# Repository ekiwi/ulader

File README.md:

# uLader #

This project aims at creating a backup battery powered bike
lighting system.
It borrows from the great work done by the developers of the
Forumslader and acknowledges this by incorporation
Lader (german for charger) into its name.
The u stands for the micro controller used in this design,
the use of which is going to add a lot more flexibility.

## Component Overview ##

The uLader system consists of these components:
* Main Board: atmega88 uC, ac to dc circuit, charging circuit, 
control switches
* Tail Light: red low power led (dimmable), photo transistor
* Front Light: attiny uC, white low power DLR (dimmabel), white 3W led 
(dimmable), photo transistor
* 2x Rotation Sensor: front and back

## Optional/Future Features ##
* White LED(s) underneath the saddle that can be turned on to find your locks
keyhole
* Pressure Sensor underneath/in the saddle to detect if someone is riding the
bike
* Turn signals on front and back

### Main Board ###

The main board contains the circuit that converts the power from the bike
dynamo, which acts approximately like an AC current source, to about 12V DC.
This circuit is heavily based on the awesome work done by the people behind
the [Forumslader project](forumslader.de).
This circuit is also responsible for charging the LiFePo4 accumulators used.
Check out [forumnslader.de]
(http://www.forumslader.de/Akkus-fuer-12V-Lader.189.0.html) if you want to use
different batteries.

The micro controller part of the Main Board features an atmega88. It was choosen,
because of its ease of use, its low power consumption and because if the number
of pins available.
The atmega is used for the following:
* power mangagement
    * check charging status
    * (indicate status??)
    * cut of power to all devices when battery cells run low
* lighting control
    * measure light intensity
    * measure speed
    * control which lights need to be on and how bright they need to be
    * in auto mode decide when to turn on which lights and auto dim

### Tail Light ####

The Tail Light needs to ensure visibility during the night (and day) from the 
back as well as from the side. In addition to that it must not blind other 
people.  
The CAT4201 led step down driver is used in combination with an OSRAM Top LED
in order to provide a low power solution for these requirements. The tail
light also includes a photo transistor for measuring the ambient light.  
It should be tested if visibility from the side of your bike can be enhanced
by adding one LED on each side.

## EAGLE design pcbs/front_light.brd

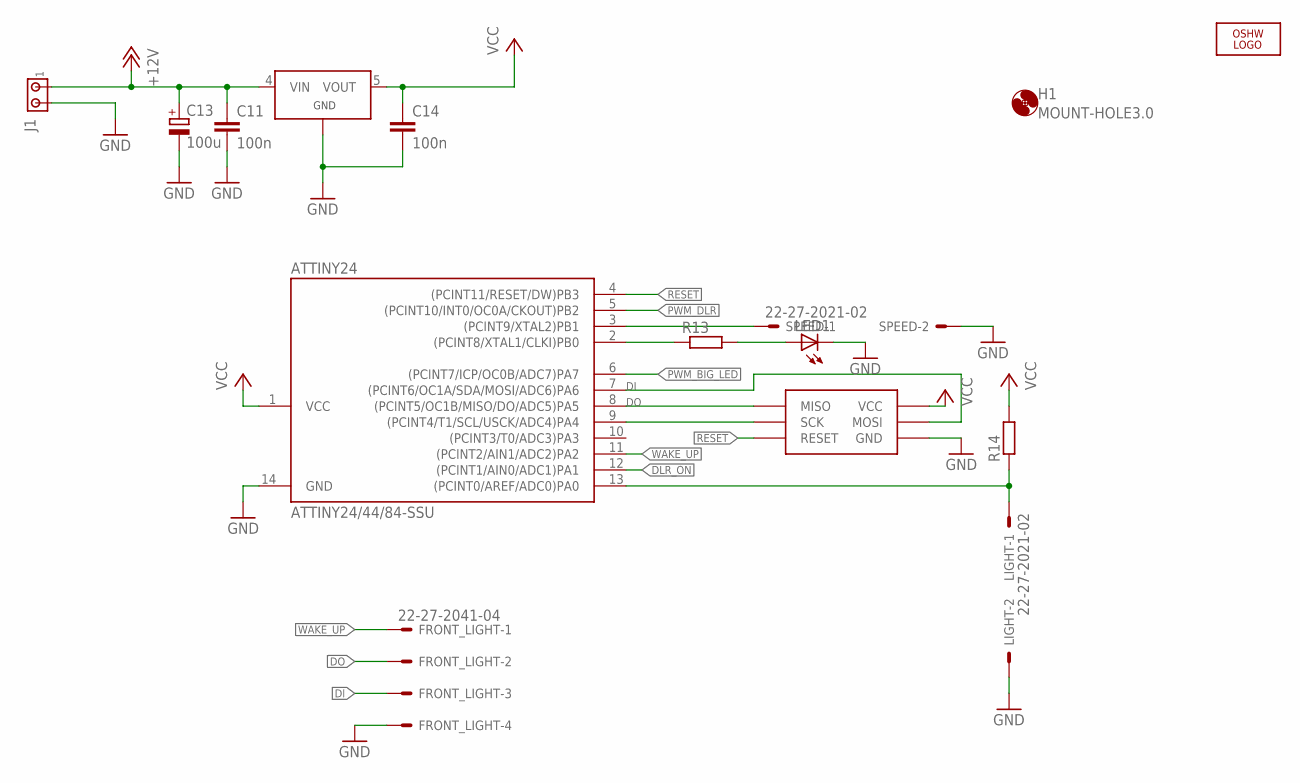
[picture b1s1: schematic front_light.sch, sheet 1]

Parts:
ATTINY24: ATTINY24/44/84-SSU; SOIC14
C11, C14: 100n; C0603
C13: 100u; PANASONIC_E
FRONT_LIGHT: 22-27-2041-04; 6410-04
H1: MOUNT-HOLE3.0; 3,0
J1: MTA02-156; 1X2MTA
LED1: LEDCHIPLED_0603; CHIPLED_0603
LIGHT: 22-27-2021-02; 6410-02
LOGO2: OSHW_LOGO_6MILX0150-NT; OSHW_6X150_NOTEXT
R13, R14: R-EU_R0603; R0603
SPEED: 22-27-2021-02; 6410-02
U$1: TPS71530; SOT23-DBV
U$2: ISP_SPECIALS; ISP_RM2_00_STRAIGHT

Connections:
+12V: C11.1, C13.+, J1.1, U$1.4 (VIN); also elsewhere on the board
DI: ATTINY24.7 ((PCINT6/OC1A/SDA/MOSI/ADC6)PA6), FRONT_LIGHT.3, U$2.MOSI
DLR_ON: ATTINY24.12 ((PCINT1/AIN0/ADC1)PA1); also elsewhere on the board
DO: ATTINY24.8 ((PCINT5/OC1B/MISO/DO/ADC5)PA5), FRONT_LIGHT.2, U$2.RESET (MISO)
GND: ATTINY24.14 (GND), C11.2, C13.-, C14.2, FRONT_LIGHT.4, J1.2, LED1.C, LIGHT.2, SPEED.2, U$1.2 (GND), U$2.VCC (GND); also elsewhere on the board
unnamed: ATTINY24.3 ((PCINT9/XTAL2)PB1), SPEED.1
unnamed: ATTINY24.9 ((PCINT4/T1/SCL/USCK/ADC4)PA4), U$2.SCK
unnamed: ATTINY24.13 ((PCINT0/AREF/ADC0)PA0), LIGHT.1, R14.1
unnamed: ATTINY24.2 ((PCINT8/XTAL1/CLKI)PB0), R13.1
unnamed: LED1.A, R13.2
PWM_BIG_LED: ATTINY24.6 ((PCINT7/ICP/OC0B/ADC7)PA7); also elsewhere on the board
PWM_DLR: ATTINY24.5 ((PCINT10/INT0/OC0A/CKOUT)PB2); also elsewhere on the board
RESET: ATTINY24.4 ((PCINT11/RESET/DW)PB3), U$2.MISO (RESET)
VCC: ATTINY24.1 (VCC), C14.1, R14.2, U$1.5 (VOUT), U$2.GND (VCC)
WAKE_UP: ATTINY24.11 ((PCINT2/AIN1/ADC2)PA2), FRONT_LIGHT.1

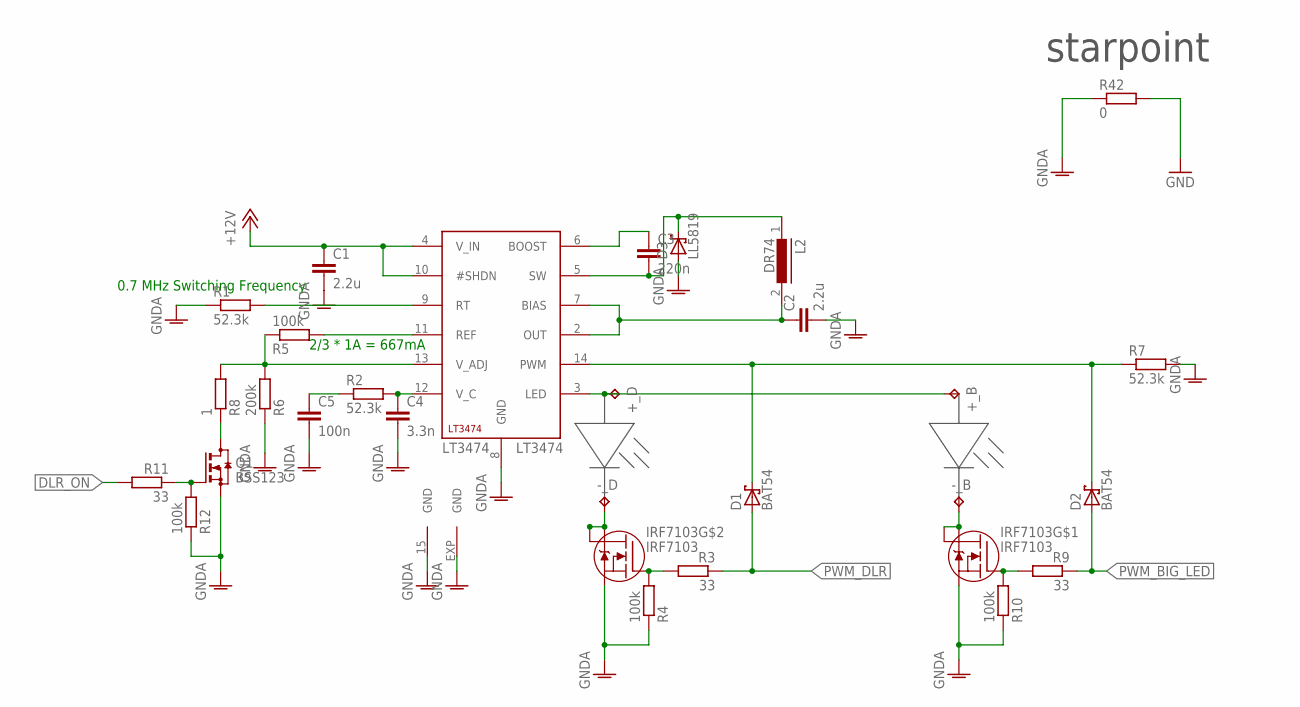
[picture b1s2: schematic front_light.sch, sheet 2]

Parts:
+_B: TPTP20SQ; TP20SQ
+_D: TPTP20SQ; TP20SQ
-_B: TPTP20SQ; TP20SQ
-_D: TPTP20SQ; TP20SQ
C1, C2: 2.2u; C0805
C3: 220n; C0603
C4: 3.3n; C0603
C5: 100n; C0603
D1, D2: BAT54; SOT23
D3: LL5819; MELF-MLL41
IRF7103: IRF7103; SO8-2
L2: DR74
LT3474: LT3474; TSSOP16_BA
Q1: BSS123; SOT23
R1, R2, R7: 52.3k; R0603
R3, R9, R11: 33; R0603
R4, R5, R10, R12: 100k; R0603
R6: 200k; R0603
R8: 1; R0603
R42: 0; R0603

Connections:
+12V: C1.1, LT3474.4 (V_IN), LT3474.10 (#SHDN); also elsewhere on the board
DLR_ON: R11.2; also elsewhere on the board
GND: R42.2; also elsewhere on the board
GNDA: C1.2, C2.2, C4.2, C5.2, D3.A, IRF7103.1 (S), IRF7103.3 (S), LT3474.8 (GND), LT3474.15 (GND), LT3474.EXP (GND), Q1.2 (S), R1.1, R4.1, R6.1, R7.2, R10.1, R12.1, R42.1
unnamed: C3.2, D3.C, L2.1, LT3474.5 (SW)
unnamed: C2.1, L2.2, LT3474.2 (OUT), LT3474.7 (BIAS)
unnamed: LT3474.11 (REF), R5.2
unnamed: LT3474.9 (RT), R1.2
unnamed: C3.1, LT3474.6 (BOOST)
unnamed: C4.1, LT3474.12 (V_C), R2.2
unnamed: C5.1, R2.1
unnamed: +_B.TP, +_D.TP, LT3474.3 (LED)
unnamed: -_D.TP, IRF7103.5 (D), IRF7103.6 (D)
unnamed: IRF7103.4 (G), R3.2, R4.2
unnamed: LT3474.13 (V_ADJ), R5.1, R6.2, R8.2
unnamed: Q1.3 (D), R8.1
unnamed: Q1.1 (G), R11.1, R12.2
unnamed: -_B.TP, IRF7103.7 (D), IRF7103.8 (D)
unnamed: IRF7103.2 (G), R9.2, R10.2
PWM: D1.3 (C), D2.3 (C), LT3474.14 (PWM), R7.1
PWM_BIG_LED: D2.1 (A), R9.1; also elsewhere on the board
PWM_DLR: D1.1 (A), R3.1; also elsewhere on the board

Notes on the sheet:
0.7 MHz Switching Frequency
2/3 * 1A = 667mA
starpoint

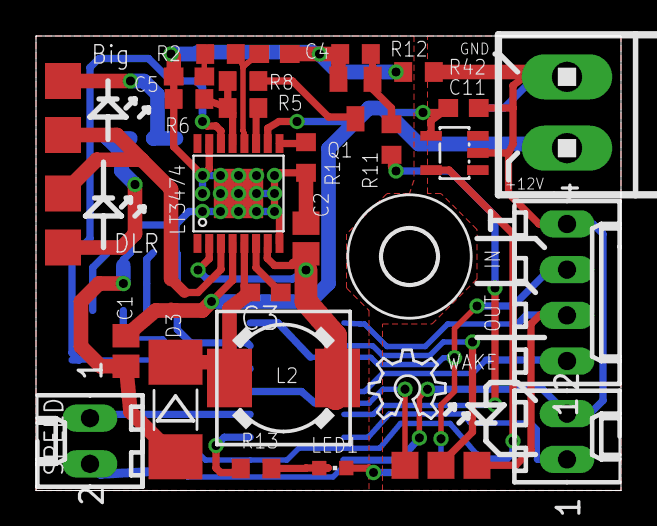
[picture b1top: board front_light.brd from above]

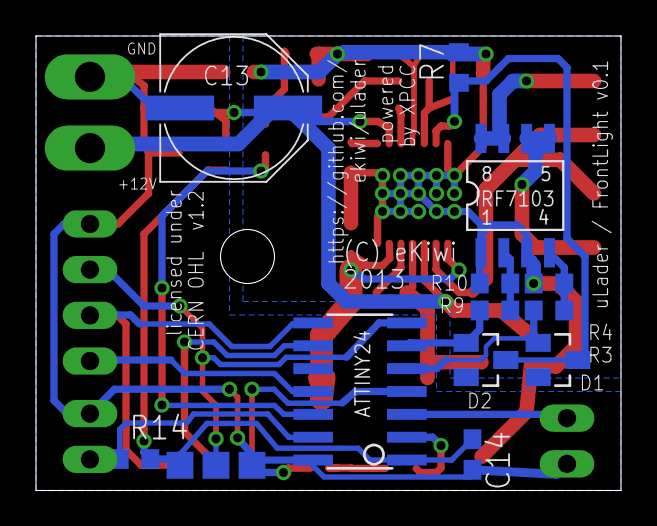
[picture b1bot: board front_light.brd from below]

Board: 2 copper layers, 32.5 x 25.2 mm, 44 parts (12 on the bottom side), 32 nets.

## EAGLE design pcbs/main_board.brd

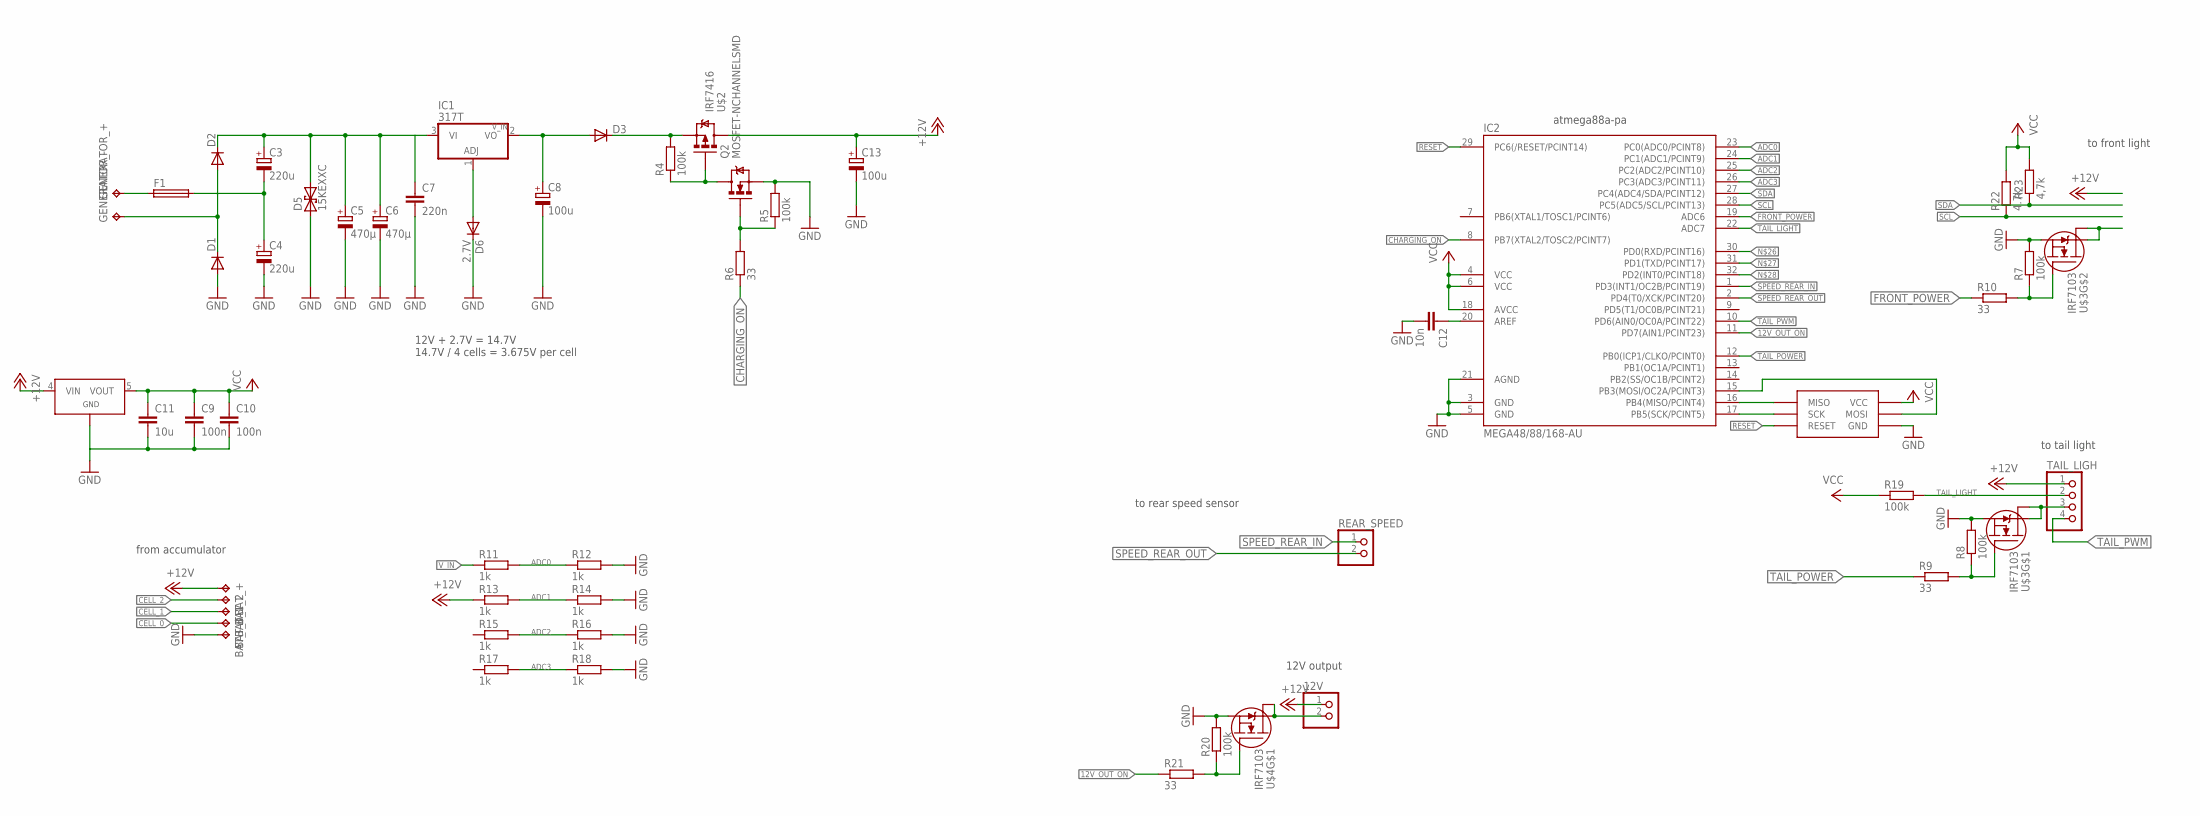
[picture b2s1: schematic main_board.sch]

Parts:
12V: PINHD-1X2; 1X02
BAT_0, BAT_1, BAT_2: TPTP18SQ; TP18SQ
BAT_+: TPTP18SQ; TP18SQ
BAT_-: TPTP18SQ; TP18SQ
C3, C4: 220u; PANASONIC_F
C5, C6: 470µ; 153CLV-1014
C7: 220n; C0805
C8, C13: 100u; PANASONIC_E
C9, C10: 100n; C0805
C11: 10u; C1206
C12: 10n; C0805
D1, D2, D3: DIODE-DO-214AC; DO-214AC
D5: 15KEXXC; CB429-17
D6: 2.7V; MINIMELF
F1: TE5
GENERATOR_+: TPTP18SQ; TP18SQ
GENERATOR_-: TPTP18SQ; TP18SQ
IC1: 317T; TO220H
IC2: MEGA48/88/168-AU; TQFP32-08
Q2: MOSFET-NCHANNELSMD; SOT23-3
R4, R5, R7, R8, R19, R20: 100k; R0603
R6, R9, R10, R21: 33; R0603
R11, R12, R13, R14, R15, R16, R17, R18: 1k; R0603
R22: 4.7k; R0603
R23: 4,7k; R0603
REAR_SPEED: PINHD-1X2; 1X02
TAIL_LIGH: PINHD-1X4; 1X04
U$1: TPS71530; SOT23-DBV
U$2: IRF7416; SO8-2
U$3, U$4: IRF7103; SO8-2
U$5: ISP_SPECIALS; ISP_RM2_00_STRAIGHT

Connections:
12V_OUT_ON: IC2.11 (PD7(AIN1/PCINT23)), R21.1
+12V: 12V.1, BAT_+.TP, C13.+, R13.1, TAIL_LIGH.1, U$1.4 (VIN), U$2.5 (D1), U$2.6 (D1), U$2.7 (D1), U$2.8 (D1)
ADC0: IC2.23 (PC0(ADC0/PCINT8)), R11.2, R12.1
ADC1: IC2.24 (PC1(ADC1/PCINT9)), R13.2, R14.1
ADC2: IC2.25 (PC2(ADC2/PCINT10)), R15.2, R16.1
ADC3: IC2.26 (PC3(ADC3/PCINT11)), R17.2, R18.1
CELL_0: BAT_0.TP
CELL_1: BAT_1.TP
CELL_2: BAT_2.TP
CHARGING_ON: IC2.8 (PB7(XTAL2/TOSC2/PCINT7)), R6.1
FRONT_POWER: IC2.19 (ADC6), R10.1
GND: BAT_-.TP, C4.-, C5.-, C6.-, C7.2, C8.-, C9.2, C10.2, C11.2, C12.2, C13.-, D1.A, D5.A (1), D6.C, IC2.3 (GND), IC2.5 (GND), IC2.21 (AGND), Q2.2 (S), R5.2, R7.2, R8.2, R12.2, R14.2, R16.2, R18.2, R20.2, U$1.2 (GND), U$3.1 (S), U$3.3 (S), U$4.1 (S), U$5.VCC (GND)
unnamed: D3.C, R4.2, U$2.1 (S1), U$2.2 (S1), U$2.3 (S1)
unnamed: C12.1, IC2.20 (AREF)
unnamed: D1.C, D2.A, GENERATOR_-.TP
unnamed: 12V.2, U$4.7 (D), U$4.8 (D)
unnamed: IC2.17 (PB5(SCK/PCINT5)), U$5.SCK
unnamed: C3.-, C4.+, F1.2
unnamed: F1.1, GENERATOR_+.TP
unnamed: D6.A, IC1.1 (ADJ)
unnamed: IC2.16 (PB4(MISO/PCINT4)), U$5.RESET (MISO)
unnamed: U$3.5 (D), U$3.6 (D)
unnamed: Q2.3 (D), R4.1, U$2.4 (G)
unnamed: Q2.1 (G), R5.1, R6.2
unnamed: TAIL_LIGH.3, U$3.7 (D), U$3.8 (D)
unnamed: R7.1, R10.2, U$3.4 (G)
unnamed: R8.1, R9.2, U$3.2 (G)
unnamed: IC2.15 (PB3(MOSI/OC2A/PCINT3)), U$5.MOSI
unnamed: R20.1, R21.2, U$4.2 (G)
unnamed: C8.+, D3.A, IC1.2 (VO)
RESET: IC2.29 (PC6(/RESET/PCINT14)), U$5.MISO (RESET)
SCL: IC2.28 (PC5(ADC5/SCL/PCINT13)), R22.1
SDA: IC2.27 (PC4(ADC4/SDA/PCINT12)), R23.1
SPEED_REAR_IN: IC2.1 (PD3(INT1/OC2B/PCINT19)), REAR_SPEED.1
SPEED_REAR_OUT: IC2.2 (PD4(T0/XCK/PCINT20)), REAR_SPEED.2
TAIL_LIGHT: IC2.22 (ADC7), R19.2, TAIL_LIGH.2
TAIL_POWER: IC2.12 (PB0(ICP1/CLKO/PCINT0)), R9.1
TAIL_PWM: IC2.10 (PD6(AIN0/OC0A/PCINT22)), TAIL_LIGH.4
VCC: C9.1, C10.1, C11.1, IC2.4 (VCC), IC2.6 (VCC), IC2.18 (AVCC), R19.1, R22.2, R23.2, U$1.5 (VOUT), U$5.GND (VCC)
V_IN: C3.+, C5.+, C6.+, C7.1, D2.C, D5.C (2), IC1.3 (VI), R11.1

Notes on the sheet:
atmega88a-pa
to front light
to tail light
from accumulator
to rear speed sensor
12V output
12V + 2.7V = 14.7V 14.7V / 4 cells = 3.675V per cell

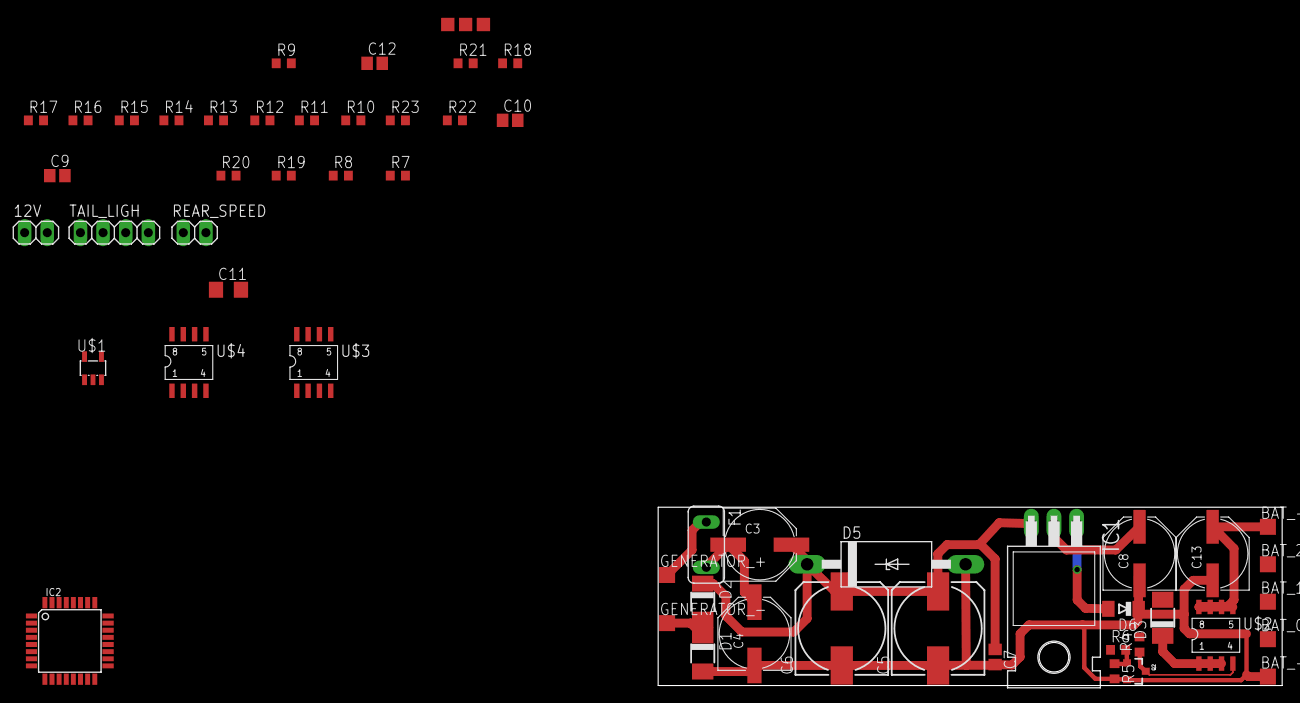
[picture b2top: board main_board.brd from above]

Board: 2 copper layers, 70.0 x 20.0 mm, 55 parts (0 on the bottom side), 37 nets.

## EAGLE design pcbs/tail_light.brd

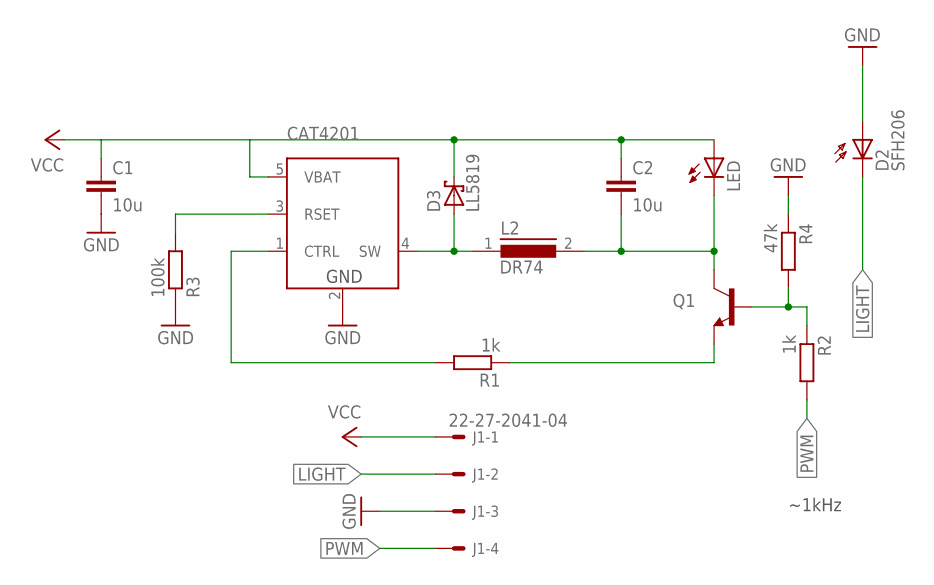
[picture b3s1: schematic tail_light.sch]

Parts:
C1, C2: 10u; C0805
CAT4201: CAT4201TF; SOT23-DBV
D2: SFH206
D3: LL5819; MELF-MLL41
J1: 22-27-2041-04; 6410-04
L2: DR74
LED: LEDMINI-TOP; OSRAM-MINI-TOP-LED
Q1: TRANSISTOR_NPNSOT23-3; SOT23-3
R1, R2: 1k; R1206
R3: 100k; R1206
R4: 47k; R1206

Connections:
GND: C1.2, CAT4201.2 (GND), D2.A, J1.3, R3.1, R4.1
LED_C: C2.2, L2.2, LED.C, Q1.3 (C)
LIGHT: D2.K (C), J1.2
unnamed: CAT4201.1 (CTRL), R1.2
unnamed: Q1.1 (B), R2.1, R4.2
unnamed: Q1.2 (E), R1.1
unnamed: CAT4201.4 (SW), D3.A, L2.1
unnamed: CAT4201.3 (RSET), R3.2
PWM: J1.4, R2.2
VCC: C1.1, C2.1, CAT4201.5 (VBAT), D3.C, J1.1, LED.A

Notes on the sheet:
~1kHz

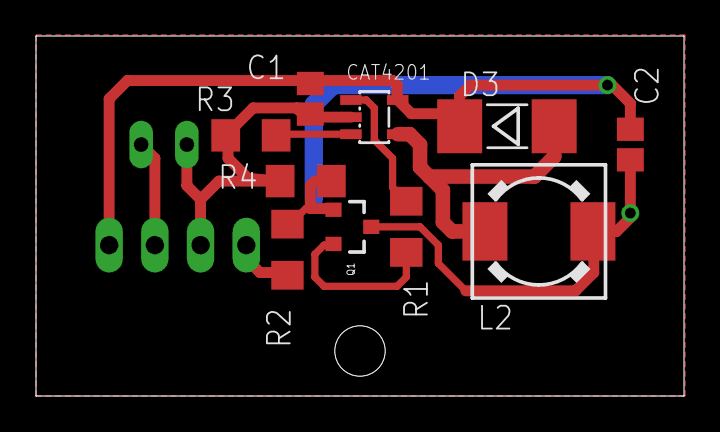
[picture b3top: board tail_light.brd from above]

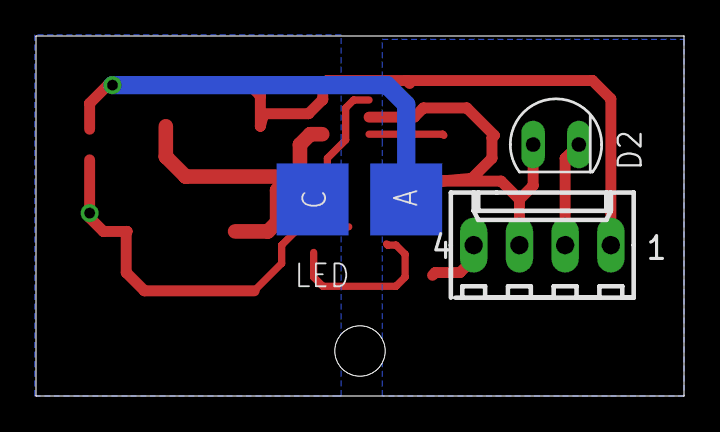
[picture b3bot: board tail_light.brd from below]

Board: 2 copper layers, 36.0 x 20.0 mm, 13 parts (3 on the bottom side), 10 nets.

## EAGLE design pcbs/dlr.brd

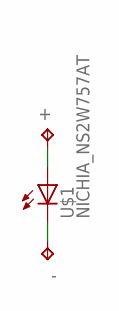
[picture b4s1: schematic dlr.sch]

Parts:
+: TPTP20SQ; TP20SQ
-: TPTP20SQ; TP20SQ
U$1: NICHIA_NS2W757AT

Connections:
+: +.TP, U$1.ANODE (A)
-: -.TP, U$1.CATHODE (C)

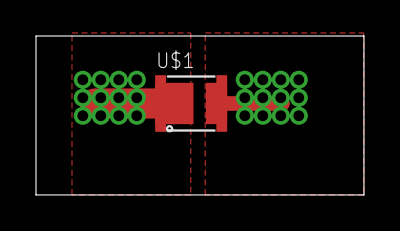
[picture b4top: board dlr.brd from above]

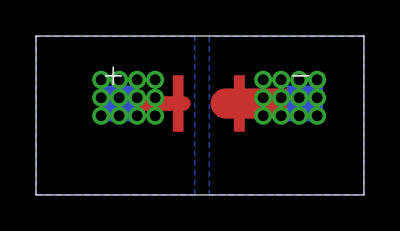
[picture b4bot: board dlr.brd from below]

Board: 2 copper layers, 18.2 x 8.8 mm, 3 parts (2 on the bottom side), 2 nets.

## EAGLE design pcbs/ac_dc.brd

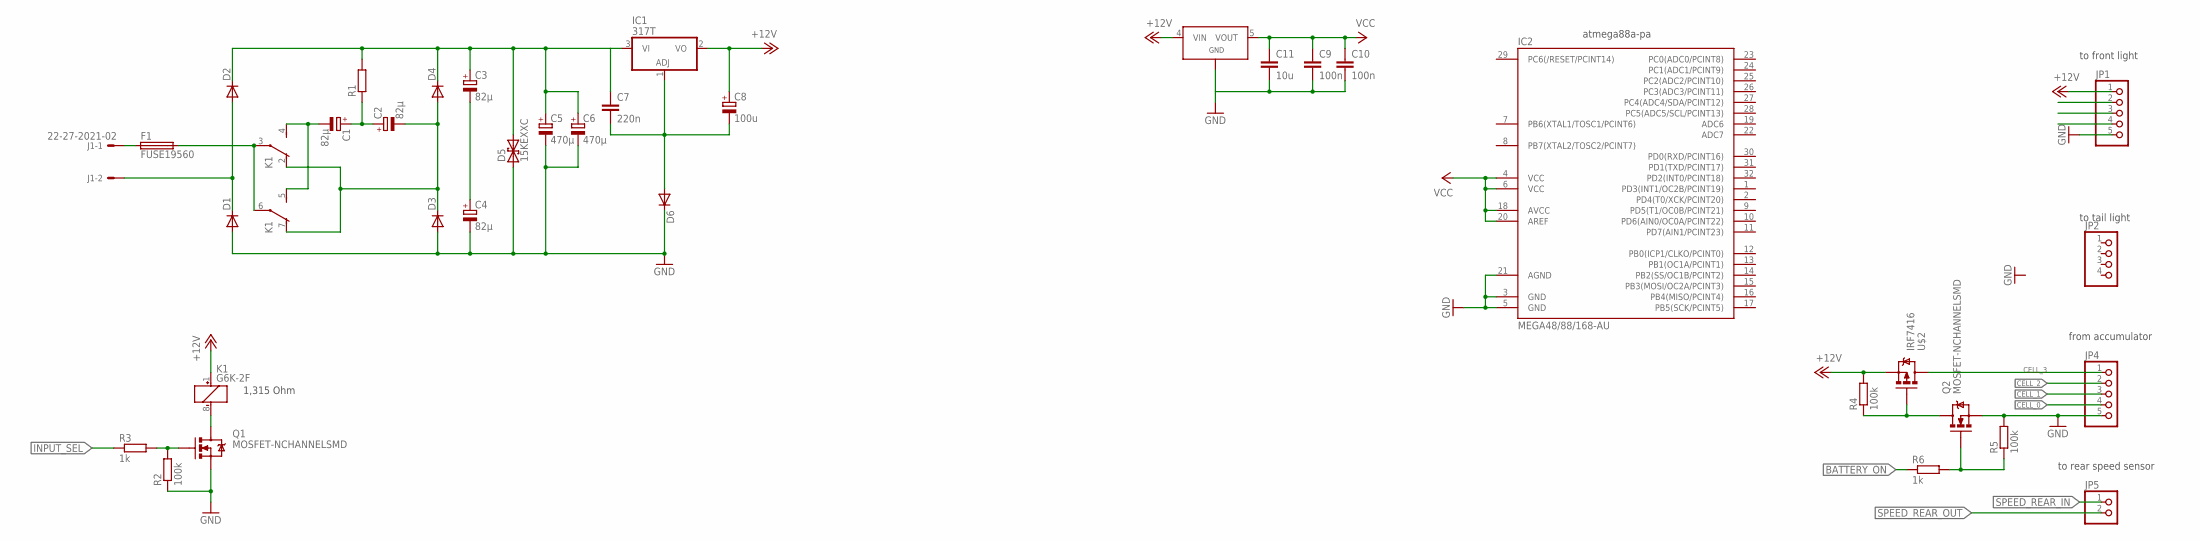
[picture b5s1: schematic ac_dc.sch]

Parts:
C1, C2, C3, C4: 82µ; 175TMP-0808
C5, C6: 470µ; 153CLV-1014
C7: 220n; C0805
C8: 100u; PANASONIC_E
C9, C10: 100n; C0805
C11: 10u; C1206
D1, D2, D3, D4: DIODE-DO-214AC; DO-214AC
D5: 15KEXXC; CB429-17
D6: DIODE-MINIMELF; MINIMELF
F1: FUSE19560; 19560
IC1: 317T; TO220H
IC2: MEGA48/88/168-AU; TQFP32-08
J1: 22-27-2021-02; 6410-02
JP1, JP4: PINHD-1X5; 1X05
JP2: PINHD-1X4; 1X04
JP5: PINHD-1X2; 1X02
K1: G6K-2F
Q1, Q2: MOSFET-NCHANNELSMD; SOT23-3
R1: R-EU_R1206; R1206
R2, R4, R5: 100k; R0805
R3, R6: 1k; R0805
U$1: TPS71530; SOT23-DBV
U$2: IRF7416; SO8-2

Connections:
+12V: C8.+, IC1.2 (VO), JP1.1, K1.1 (+), R4.2, U$1.4 (VIN), U$2.1 (S1), U$2.2 (S1), U$2.3 (S1)
BATTERY_ON: R6.1
CELL_0: JP4.4
CELL_1: JP4.3
CELL_2: JP4.2
CELL_3: JP4.1, U$2.5 (D1), U$2.6 (D1), U$2.7 (D1), U$2.8 (D1)
GND: C4.-, C5.-, C6.-, C9.2, C10.2, C11.2, D1.A, D3.A, D5.A (1), D6.C, IC2.3 (GND), IC2.5 (GND), IC2.21 (AGND), JP1.5, JP4.5, Q1.2 (S), Q2.2 (S), R2.1, R5.2, U$1.2 (GND)
INPUT_SEL: R3.1
unnamed: C3.-, C4.+
unnamed: C2.-, D3.C, D4.A, K1.2 (O), K1.7 (O)
unnamed: C1.+, C2.+, R1.1
unnamed: D1.C, D2.A, J1.2
unnamed: C3.+, C5.+, C6.+, C7.1, D2.C, D4.C, D5.C (2), IC1.3 (VI), R1.2
unnamed: C1.-, K1.4 (S), K1.5 (S)
unnamed: F1.2, K1.3, K1.6
unnamed: F1.1, J1.1
unnamed: C7.2, C8.-, D6.A, IC1.1 (ADJ)
unnamed: K1.8 (-), Q1.3 (D)
unnamed: Q1.1 (G), R2.2, R3.2
unnamed: Q2.3 (D), R4.1, U$2.4 (G)
unnamed: Q2.1 (G), R5.1, R6.2
SPEED_REAR_IN: JP5.1
SPEED_REAR_OUT: JP5.2
VCC: C9.1, C10.1, C11.1, IC2.4 (VCC), IC2.6 (VCC), IC2.18 (AVCC), IC2.20 (AREF), U$1.5 (VOUT)

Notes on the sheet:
atmega88a-pa
to front light
to tail light
1,315 Ohm
from accumulator
to rear speed sensor

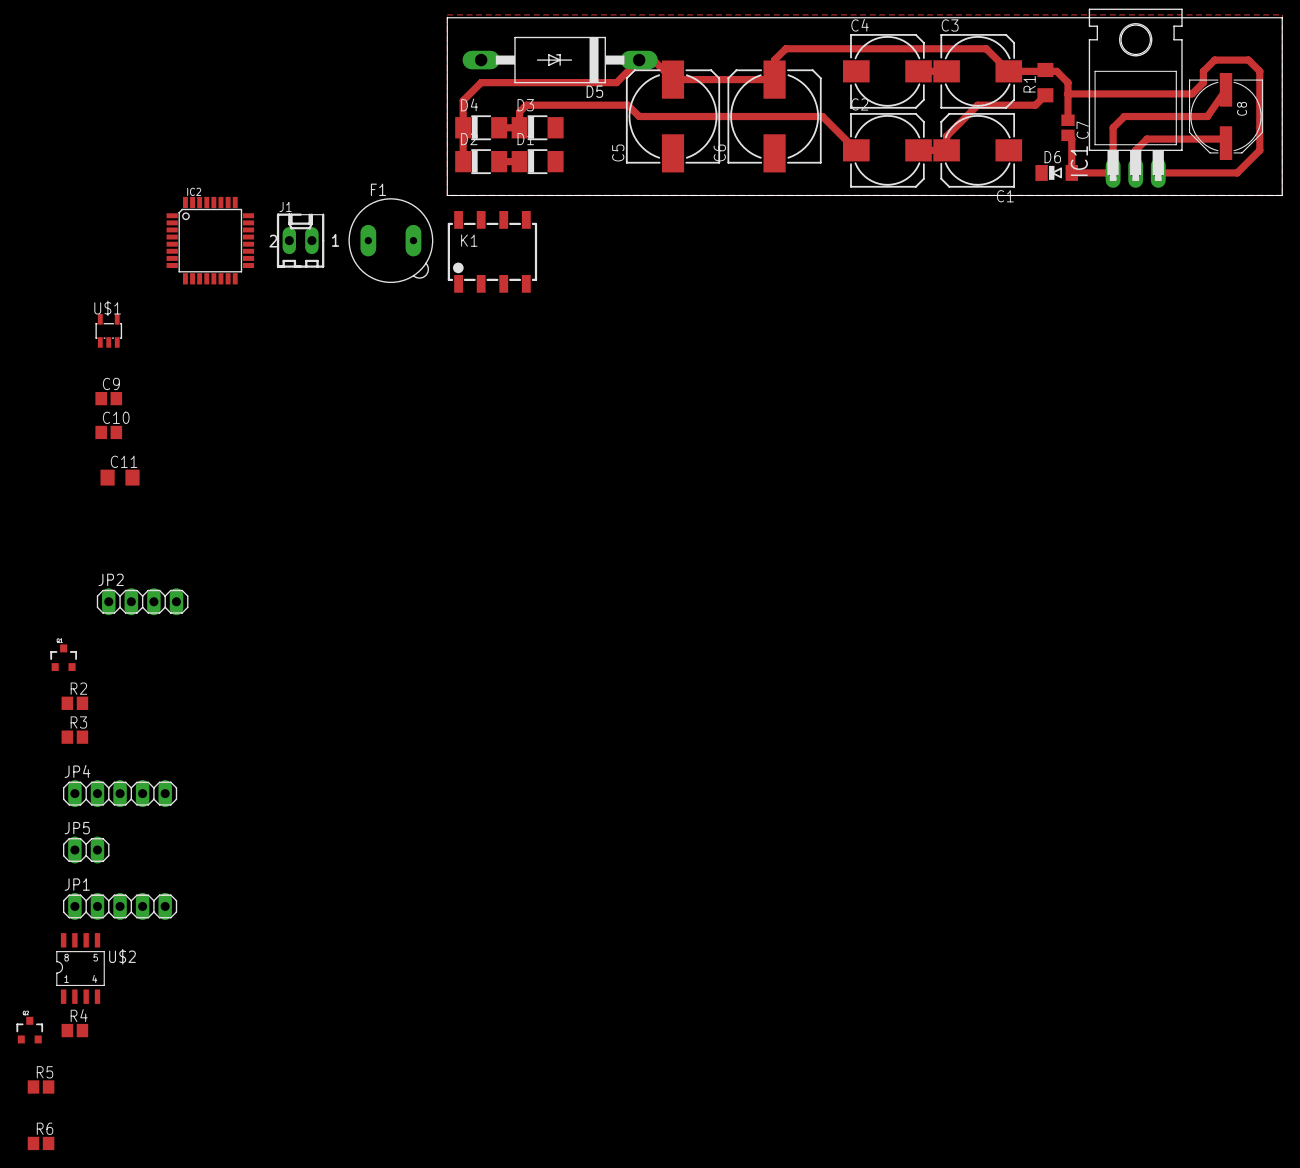
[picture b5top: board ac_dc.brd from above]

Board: 2 copper layers, 94.0 x 20.0 mm, 36 parts (0 on the bottom side), 17 nets.

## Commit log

2012-10-03 Added initial gitignore file for eagle pcbs
2012-10-03 Added initial pcbs
2012-10-03 README: Added short description.
2012-10-03 gitignore: Ignore gedit backup files (*~)
2012-10-03 AC/DC: Added atmega88 and power supply.
2012-10-05 Readme: Added component overview and main board info.
2012-10-05 Readme: added main board and tail light description.
2012-10-07 Main Board: Added battery connector + mosfet switch
2012-10-07 Renamed ac_dc.* to main_board.*
2012-10-07 Main Board: Added connections to front and to tail light.
2012-10-07 Main Board: Expanded Board to 120 x 20 mm
2012-10-08 Main Board: Changed fuse and corrected wrong connection.
2012-10-08 Main Board: Added resistor dividers for voltage measurements.
2012-10-08 Main Board: Added switchable 12V output.
2012-10-08 Main Board: added i2c pullups.
2012-10-08 Main Board: Changed battery connection.
    It does not make sense to disconnect the battery from the uC....
    Instead it makes sense to disconnect the charging/input circuit
    when the battery is full and disconnect the peripherals when it is
    getting empty.
2012-10-12 Main Board: Added back i2c
2012-10-12 Main Board: Started layouting control part
2012-11-19 Readme: Added "Optional/Feature" Features
2013-09-29 Main: fixed inconsitency between sch and brd
2013-09-29 Front light: use attiny and LT3474
2013-09-29 ForntLight: improved silkscreen
2013-09-29 FrontLight: solved some DRC errors
    If the .dru file from OSH Park is used
    and clearance od same signal smd, pad and via
    is set to 0, we do not get any DRC errors.
2013-09-30 FrontLight: use only one LT3474
    Since the DLR and the big led will never be used
    together they can be driven by a single
    led constant current switching IC.
2013-09-30 Spice: add LTSpice simulation of front light
2013-09-30 DLR: add preliminary breakoutboard
2013-10-20 Front Light: change via drill size to 0.5mm
2014-12-09 Pcbs: latest changes

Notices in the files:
pcbs/front_light.brd:
licensed under
CERN OHL  v1.2
parts and their libraries:
SparkFun: Licensing: CC v3.0 Share-Alike You are welcome to use this library for commercial purposes.
irf-2: Copyright & License
This library is licensed under the General Public License, Version 2.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
